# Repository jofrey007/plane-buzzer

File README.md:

## Determalizátor a bzučiak pre voľné modely
Princíp uvoľnenia pohyblivej časti modelu je cez prepálenie gumičky rozpáleným odporovým drôtom.
Determalizátor sa skladá z 2 modulov

 - prijímač 433 MHz s výkonovým MOSFET tranzistorom
 - modul bzučiaka s aktívnym piezzo bzučiakom

Napájanie determalizátora je LiPo akumulátorom 1S (3.7V), 35mAh, ktoré sa používajú do BT slúchadiel.

### Programovanie Attiny402
Pre naprogramovanie plane-buzzer.ino do MCU použite nejaké iné Arduino (Uno) ?
Popis programovania je uvedený v youtube videu aj s popisom pod ním
[Programovanie cez UPDI ](https://www.youtube.com/watch?v=YOGeoW_QySs)

### PCB bzučiaka

### Odporová špirála
3 závity na vrtáku 3mm [A1 30G 100Ft](https://www.aliexpress.com/item/1005001496323840.html?spm=a2g0o.order_list.order_list_main.284.61ee1802CS6hZ)

### Háčik na zavesenie gumy

### Anténa
Pôvodnú anténu odpájkovať a nahradiť rovnako dlhým vodičom [30AWG](https://www.aliexpress.com/item/1005001590476043.html?spm=a2g0o.order_detail.order_detail_item.7.6c56f19cd0DTJT)

### Nabíjanie akumulátora
Akumulátor sa musí nabíjať malým prúdom okolo 5-10mA, z toho dôvodu je potrebné upraviť nabíjač s MCP73831. Úprava spočíva vo výmene SMD odporu za odpor s hodnotou 68k.
[nabíjačka](https://github.com/jofrey007/plane-buzzer/blob/main/hardware/charger.jpg)

## Galéria fotiek
[Google photos](https://photos.app.goo.gl/KZA55k8EkyTrNWjo8)

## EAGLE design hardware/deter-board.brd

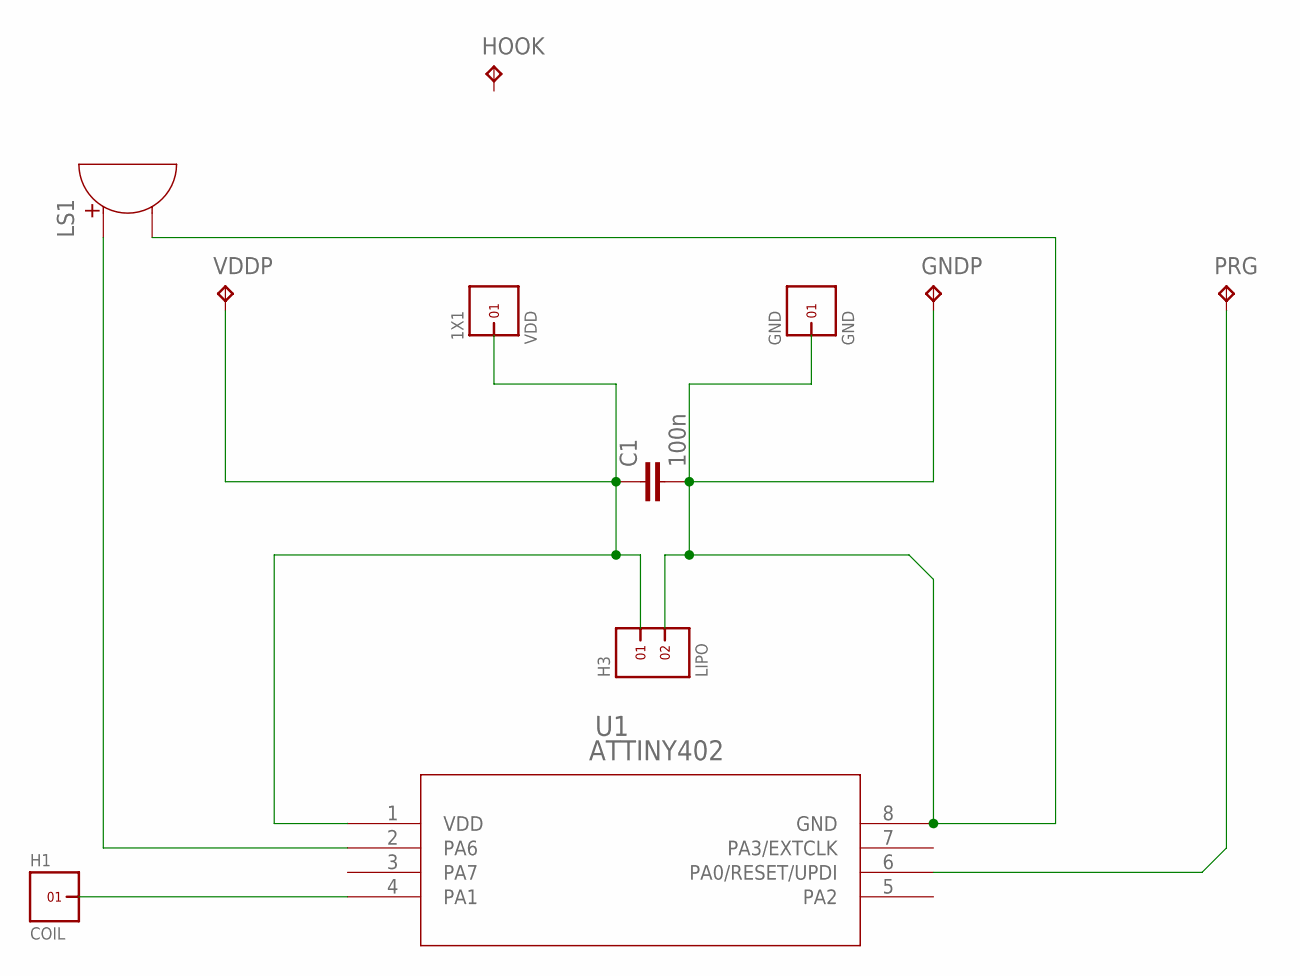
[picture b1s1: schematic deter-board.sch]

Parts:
C1: 100n; 1206
GND: GND; 1X1
GNDP: GND; B1,27
H1: COIL; 1X1
H3: LIPO; 1X2
HOOK: HOOK; P1-17Y
LS1: BUZZER_(9650); S-BUZZER-MLT-9650
PRG: PROG; B2,54
U1: ATTINY402; SOIC8_4P9X3P9MC_MCH
VDD: 1X1
VDDP: VDD; B1,27

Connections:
unnamed: LS1.P$2 (+), U1.2 (PA6)
unnamed: C1.1, H3.1, U1.1 (VDD), VDD.1, VDDP.TP
unnamed: C1.2, GND.1, GNDP.TP, H3.2, LS1.P$1 (-), U1.8 (GND)
unnamed: PRG.TP, U1.6 (PA0/RESET/UPDI)
unnamed: H1.1, U1.4 (PA1)

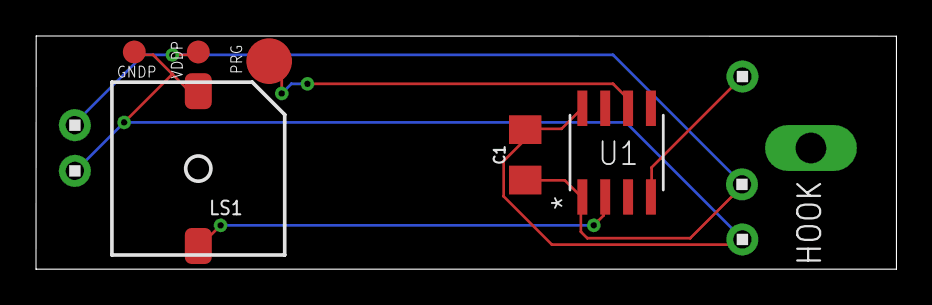
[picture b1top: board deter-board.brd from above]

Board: 2 copper layers, 47.8 x 13.0 mm, 11 parts (0 on the bottom side), 5 nets.

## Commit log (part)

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2025-01-06 prvy commit
2025-01-06 zmena nazvu suboru a pridanie suborov pre hardware
2025-01-26 upresnenie cisiel pinov
2025-03-12 pridany BOM
2025-03-12 obrazok nabijacky
2026-01-02 "Claude PR Assistant workflow"
2026-01-02 "Claude Code Review workflow"

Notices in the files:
parts and their libraries:
SparkFun-Capacitors: Licensing: Creative Commons ShareAlike 4.0 International - https://creativecommons.org/licenses/by-sa/4.0
COPYRIGHT: Copyright (C) 2024 Ultra Librarian. All rights reserved.
